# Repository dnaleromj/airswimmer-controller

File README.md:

Airswimmer Controller
======================

Randy wants a fishbowl the size of SPARC.

This PCB is a drop in replacement for the PCB in the device.

Highlights
==========
* Arduino Happy
* 2 brushed motor controllers built in (like in the original circuit)
* 2.4GHZ radio (Phase 2)
* Accellerometer and Gyro built in the so the fish can go where it wants.
* LIPO - 2S right now,  will consider 1S later.

Phase 1
=======

* PCB drawn and sent to the FAB
* Initial Firmware will be made that implements simple autonomous movements
  * Bump into something, move in a different direction
  * Get bored and scoot at random times.
  * 

Phase 2
=======

* Bluetoth/BT Low Enegery on board for iPhone/iPad control
  *  Will support a serial stream command mode
  *  regurgitate onboard stats, battery level,  log of decisions, etc.

Phase 3
=======

* You tell me!

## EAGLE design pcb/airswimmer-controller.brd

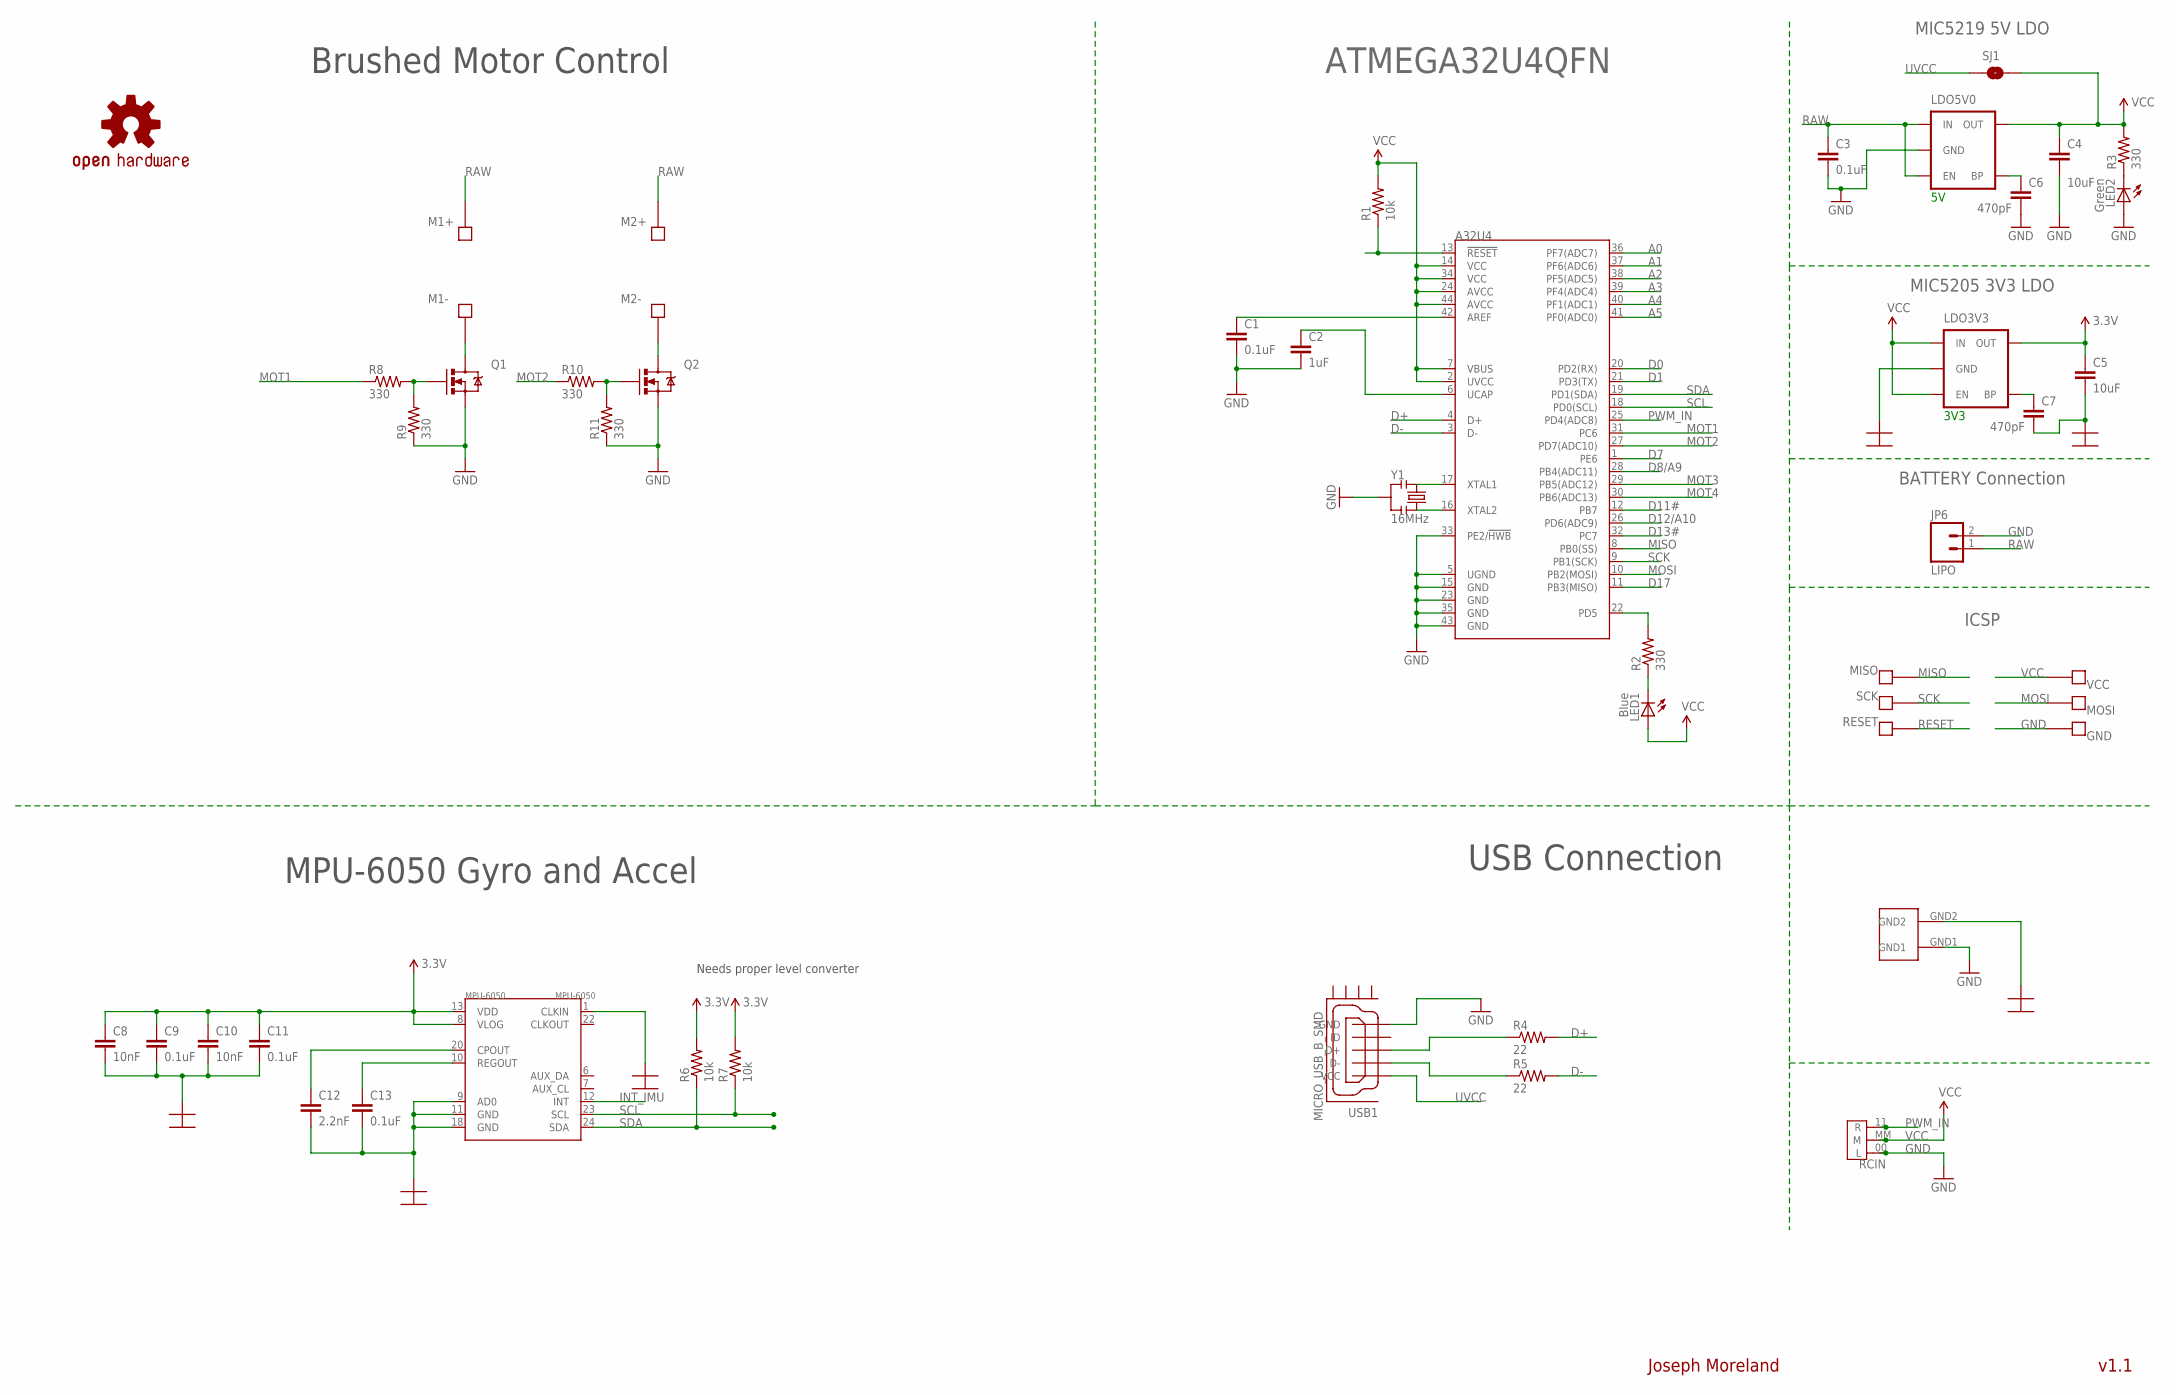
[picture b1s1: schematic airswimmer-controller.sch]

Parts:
A32U4: ATMEGA32U4QFN; ATMEL_QFN-44_SMALL_PAD; PARTNO ATMEGA32U4-MU
C1, C3: 0.1uF; SPARKFUN_0402-CAP; PARTNO GMK105BJ104KV-F
C2: 1uF; SPARKFUN_0402-CAP; PARTNO LMK105BJ105KV-F
C4, C5: 10uF; 0603-CAP; PARTNO TCM1A106M8R
C6, C7: 470pF; 0603-CAP; PARTNO C0603C471K5RACTU
C8, C10: 10nF; 0402-CAP; PARTNO C0402C103K8RACTU
C9, C11, C13: 0.1uF; 0402-CAP; PARTNO GMK105BJ104KV-F
C12: 2.2nF; 0402-CAP; PARTNO C0402C222K4RACTU
GND: TEST_PAD; ICSP_PAD; PARTNO DNP
GND_SHORT: GND_SHORT; PARTNO DNP
JP6: LIPO; 1X02_LOCK; PARTNO DNP
LDO3V3: V_REG_MIC52193.3V; SOT23-5; PARTNO MIC5219-3.3YM5 TR
LDO5V0: MIC5219; SOT23-5; PARTNO MIC5219-5.0YM5 TR
LED1: Blue; LED-0603; PARTNO LTST-C191TBKT
LED2: Green; LED-0603; PARTNO LTST-C190KGKT
LOGO1: OSHW-LOGOM; OSHW-LOGO-M; PARTNO DNP
M1+, M1-, M2+, M2-: SOLDER_PAD.05X.05; SOLDER_PAD_.05X.05; PARTNO DNP
MISO: TEST_PAD; ICSP_PAD; PARTNO DNP
MOSI: TEST_PAD; ICSP_PAD; PARTNO DNP
MPU-6050: MPU-6050; QFN-24; PARTNO *
Q1, Q2: MOSFET-NCHANNELBSS123LT1G; SOT23; PARTNO DMG6968U-7
R1, R6, R7: 10k; 0402-RES; PARTNO CRCW040210K0FKED
R2, R3, R8, R9, R10, R11: 330; 0402-RES; PARTNO CRCW0402330RJNED
R4, R5: 22; 0402-RES; PARTNO CRCW040222R0JNED
RCIN: PAD-JUMPER-3P40*40; 3P-SMD-4.1X1.5; PARTNO DNP
RESET: TEST_PAD; ICSP_PAD; PARTNO DNP
SCK: TEST_PAD; ICSP_PAD; PARTNO DNP
SJ1: P-USB; SPARKFUN_SJ_2S; PARTNO DNP
USB1: MICRO_USB_B_SMD; MOLEX_MICRO_USB_B_BOTTOM_MOUNT; PARTNO 473460001
VCC: TEST_PAD; ICSP_PAD; PARTNO DNP
Y1: 16MHz; RESONATOR-SMD; PARTNO CSTCE16M0V53-R0

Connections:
3.3V: C5.1, C8.1, C9.1, C10.1, C11.1, LDO3V3.5 (OUT), MPU-6050.8 (VLOG), MPU-6050.13 (VDD), R6.2, R7.2
A0: A32U4.36 (PF7(ADC7))
A1: A32U4.37 (PF6(ADC6))
A2: A32U4.38 (PF5(ADC5))
A3: A32U4.39 (PF4(ADC4))
A4: A32U4.40 (PF1(ADC1))
A5: A32U4.41 (PF0(ADC0))
AREF: A32U4.42 (AREF), C1.1
D0: A32U4.20 (PD2(RX))
D1: A32U4.21 (PD3(TX))
D7: A32U4.1 (PE6)
D8/A9: A32U4.28 (PB4(ADC11))
D11#: A32U4.12 (PB7)
D12/A10: A32U4.26 (PD6(ADC9))
D13#: A32U4.32 (PC7)
D17: A32U4.11 (PB3(MISO))
D+: A32U4.4 (D+), R4.2
D-: A32U4.3 (D-), R5.2
DGND: C5.2, C7.2, C8.2, C9.2, C10.2, C11.2, C12.2, C13.2, GND_SHORT.GND2, LDO3V3.2 (GND), MPU-6050.1 (CLKIN), MPU-6050.9 (AD0), MPU-6050.11 (GND), MPU-6050.18 (GND)
GND: A32U4.5 (UGND), A32U4.15 (GND), A32U4.23 (GND), A32U4.33 (PE2/!HWB), A32U4.35 (GND), A32U4.43 (GND), C1.2, C2.2, C3.2, C4.2, C6.2, GND.P$1, GND_SHORT.GND1, JP6.2, LDO5V0.2 (GND), LED2.A, Q1.2 (S), Q2.2 (S), R9.1, R11.1, RCIN.00 (L), USB1.5 (GND), Y1.2
INT_IMU: MPU-6050.12 (INT)
MISO: A32U4.8 (PB0(SS)), MISO.P$1
MOSI: A32U4.10 (PB2(MOSI)), MOSI.P$1
MOT1: A32U4.31 (PC6), R8.1
MOT2: A32U4.27 (PD7(ADC10)), R10.1
MOT3: A32U4.29 (PB5(ADC12))
MOT4: A32U4.30 (PB6(ADC13))
unnamed: R4.1, USB1.3 (D+)
unnamed: C6.1, LDO5V0.4 (BP)
unnamed: A32U4.17 (XTAL1), Y1.1
unnamed: C7.1, LDO3V3.4 (BP)
unnamed: M1-.P$1, Q1.3 (D)
unnamed: A32U4.16 (XTAL2), Y1.3
unnamed: LED1.C, R2.1
unnamed: M2-.P$1, Q2.3 (D)
unnamed: LED2.C, R3.1
unnamed: R5.1, USB1.2 (D-)
unnamed: C13.1, MPU-6050.10 (REGOUT)
unnamed: C12.1, MPU-6050.20 (CPOUT)
unnamed: Q1.1 (G), R8.2, R9.2
unnamed: Q2.1 (G), R10.2, R11.2
unnamed: A32U4.22 (PD5), R2.2
PWM_IN: A32U4.25 (PD4(ADC8)), RCIN.11 (R)
RAW: C3.1, JP6.1, LDO5V0.1 (IN), LDO5V0.3 (EN), M1+.P$1, M2+.P$1
RESET: A32U4.13 (!RESET), R1.1, RESET.P$1
SCK: A32U4.9 (PB1(SCK)), SCK.P$1
SCL: A32U4.18 (PD0(SCL)), MPU-6050.23 (SCL), R7.1
SDA: A32U4.19 (PD1(SDA)), MPU-6050.24 (SDA), R6.1
UCAP: A32U4.6 (UCAP), C2.1
UVCC: SJ1.1, USB1.1 (VCC)
VCC: A32U4.2 (UVCC), A32U4.7 (VBUS), A32U4.14 (VCC), A32U4.24 (AVCC), A32U4.34 (VCC), A32U4.44 (AVCC), C4.1, LDO3V3.1 (IN), LDO3V3.3 (EN), LDO5V0.5 (OUT), LED1.A, R1.2, R3.2, RCIN.MM (M), SJ1.2, VCC.P$1

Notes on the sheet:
3V3
MIC5219 5V LDO
MIC5205 3V3 LDO
BATTERY Connection
Joseph Moreland
v1.1
Brushed Motor Control
Needs proper level converter
ICSP
USB Connection
MPU-6050 Gyro and Accel

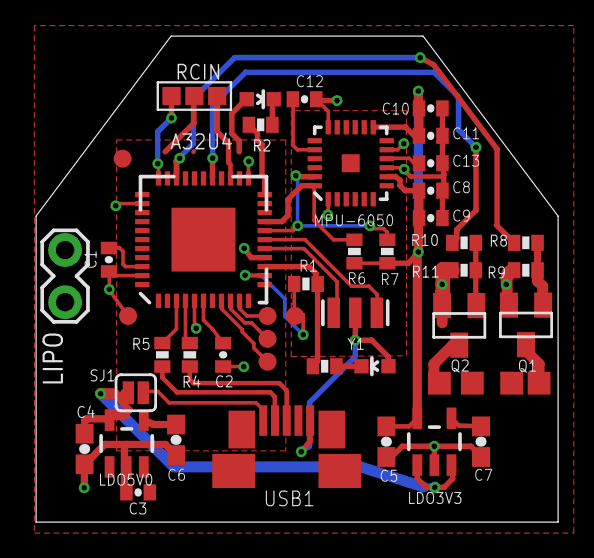
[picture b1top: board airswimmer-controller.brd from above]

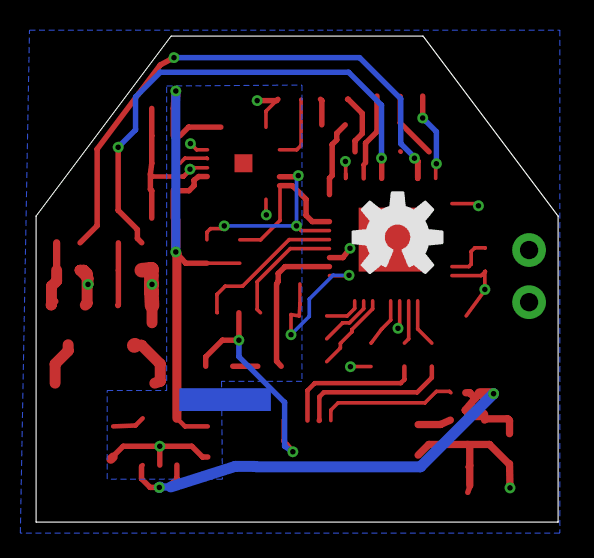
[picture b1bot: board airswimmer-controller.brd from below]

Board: 2 copper layers, 29.0 x 27.0 mm, 49 parts (2 on the bottom side), 34 nets.

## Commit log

2013-04-13 Initial repo
2013-04-23 Reorg to the standard JCM layout.
2013-04-23 Correct LED cathode direction in schematic.
2013-04-23 Correct LED cathode direction in schematic and board.
2013-04-23 Added Solidworks board drawing.

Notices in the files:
parts and their libraries:
SparkFun-Connectors: Licensing: CC v3.0 Share-Alike You are welcome to use this library for commercial purposes.
